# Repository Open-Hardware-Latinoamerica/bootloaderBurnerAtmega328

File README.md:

# bootloaderBurnerAtmega328
Shield tht version for easy arduino bootloader burning
This is a shield for burning arduino bootloader in atmega328p, it's useful when you need programming a lot of atmega328 , you can dowload the gerber files ans schematic 
#avr #hardwaredesign #kicad #arduino
Tutorial for burning bootloader
https://lnkd.in/epM4m4J

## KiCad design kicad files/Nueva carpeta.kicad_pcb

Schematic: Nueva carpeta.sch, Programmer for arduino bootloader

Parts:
C1, C2: 22pF; C_Disc_D3.0mm_W2.0mm_P2.50mm
D1: PWR; LED_D3.0mm
D2: RUN; LED_D3.0mm
D3: ERROR; LED_D3.0mm
D4: PROG; LED_D3.0mm
D5: SCK; LED_D3.0mm
P1: Power; Socket_Strip_Arduino_1x08
P2: Analog; Socket_Strip_Arduino_1x06
P3: Digital; Socket_Strip_Arduino_1x10
P4: Digital; Socket_Strip_Arduino_1x08
P5, P6, P7, P8: CONN_01X01; Arduino_1pin
R1: 10KΩ; R_Axial_DIN0207_L6.3mm_D2.5mm_P7.62mm_Horizontal
R2, R3, R4, R5, R6: 470Ω; R_Axial_DIN0207_L6.3mm_D2.5mm_P7.62mm_Horizontal
SW1: RESET; SW_PUSH_6mm
U1: ATMEGA328P-PU; DIP-28_W7.62mm_LongPads
Y1: Crystal; Crystal_HC49-4H_Vertical

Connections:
+3V3: P1.4
+5V: D1.2, P1.5, R1.2, U1.7 (VCC), U1.20 (AVCC)
/0(Rx): P4.8
/1(Tx): P4.7
/2: P4.6
/3(**): P4.5
/4: P4.4
/5(**): P4.3
/6(**): P4.2
/7: P4.1, R5.1
/8: P3.10, R4.1
/9(**): P3.9, R3.1
/10(**/SS): P3.8, R1.1, SW1.1, U1.1 ((PCINT14/~RESET~)PC6)
/11(**/MOSI): P3.7, U1.17 ((PCINT3/OC2A/MOSI)PB3)
/12(MISO): P3.6, U1.18 ((PCINT4/MISO)PB4)
/13(SCK): P3.5, R6.2, U1.19 ((PCINT5/SCK)PB5)
/A0: P2.1
/A1: P2.2
/A2: P2.3
/A3: P2.4
/A4(SDA): P2.5
/A5(SCL): P2.6
/AREF: P3.3
/IOREF: P1.2
/Reset: P1.3
/Vin: P1.8
/XTAL1: C2.1, U1.9 ((PCINT6/XTAL1/TOSC1)PB6), Y1.2
/XTAL2: C1.1, U1.10 ((PCINT7/XTAL2/TOSC2)PB7), Y1.1
GND: C1.2, C2.2, D2.1, D3.1, D4.1, D5.1, P1.6, P1.7, P3.4, R2.2, SW1.2, U1.8 (GND), U1.22 (GND)
unnamed: D1.1, R2.1
unnamed: D2.2, R3.2
unnamed: D3.2, R4.2
unnamed: D4.2, R5.2
unnamed: D5.2, R6.1

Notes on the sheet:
Holes
Shield for Arduino that uses the same pin disposition like "Uno" board Rev 3.
ATMEGA328P

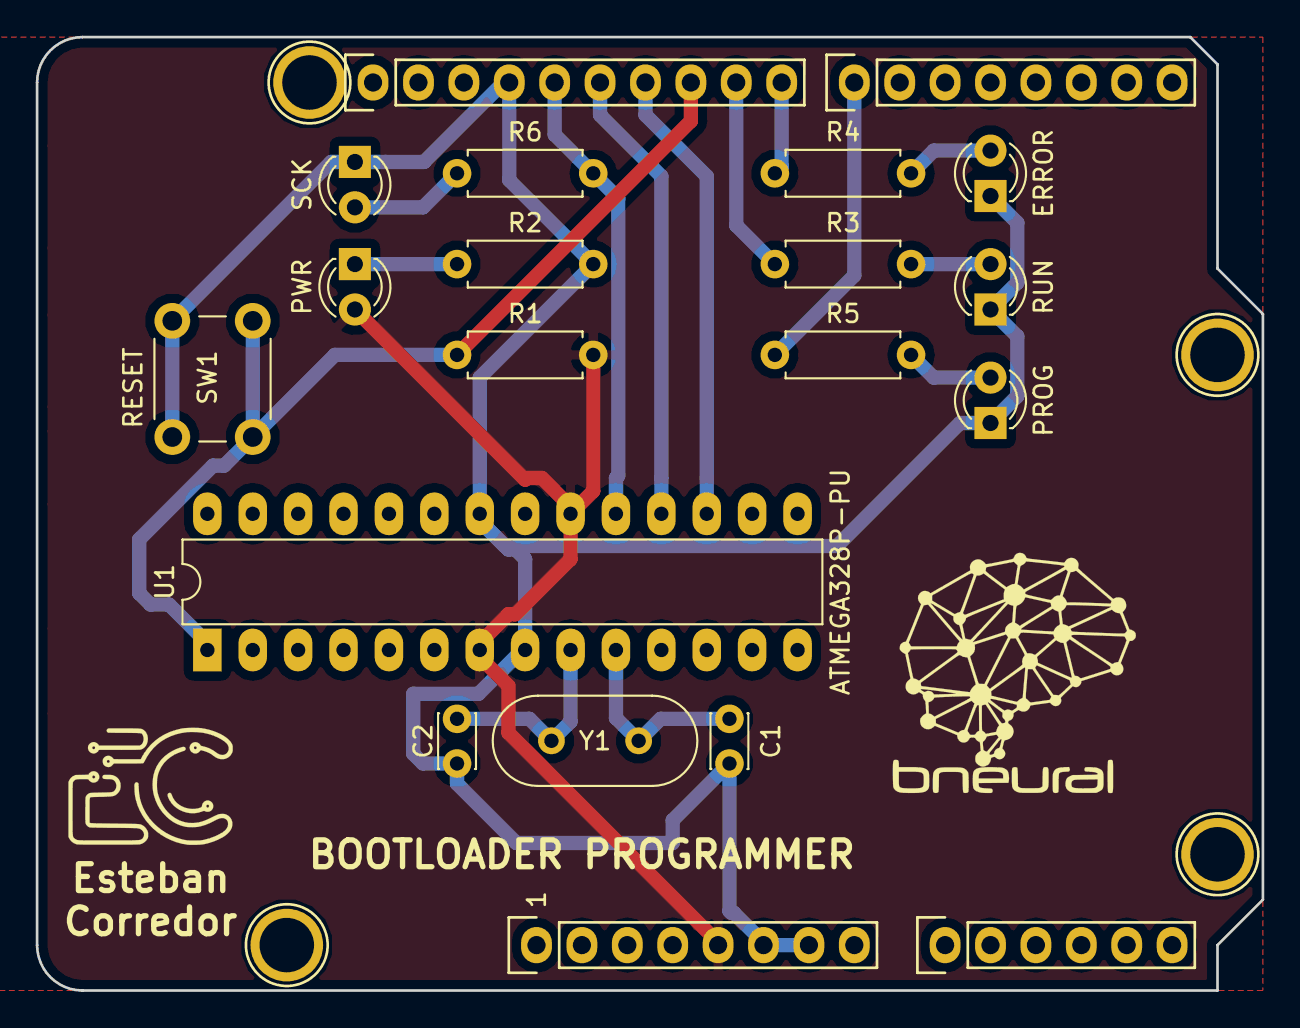
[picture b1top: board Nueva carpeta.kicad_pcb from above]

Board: 2 copper layers, 68.6 x 53.3 mm, 24 parts (0 on the bottom side), 16 nets.

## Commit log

2019-12-15 kicad files
2019-12-15 agregando .gitignore
2019-12-17 acomodando la version actual
